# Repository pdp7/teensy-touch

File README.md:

# Teensy LC cap touch demo
Capactive touch button demo board for Teensy LC with Adafruit 128x64 OLED (SPI)

## OSH Park Shared Project:
* **[Teensy LC cap touch demo](https://oshpark.com/projects/ro7ypcxO)**
   * This is what was ordered and tested
   * File: [teensy-touch.kicad_pcb](https://github.com/pdp7/teensy-touch/blob/5fb2f44a5e37c01898689bddd4195240e6bf3efe/hardware/teensy-touch.kicad_pcb)
   * Commit: [5fb2f44 *connect GND pin for OLED to GND plane*
](https://github.com/pdp7/teensy-touch/commit/5fb2f44a5e37c01898689bddd4195240e6bf3efe)

## Bill of Materials:
* [Monochrome 0.96" 128x64 OLED graphic display](https://www.adafruit.com/product/326)
* [Teensy LC, OSH Park edition](http://store.oshpark.com/products/teensy-lc)

## Videos
* [Short demo](https://www.youtube.com/watch?v=SUqngf3_1D0)
* [Full demo](https://youtu.be/iRWQk5bGx8w)

## Photos
* [Google+ gallery](https://plus.google.com/photos/+DrewFustini/albums/6318204370050037249)
* [images directory](images)

## License
This project released under the CERN Open Hardware v1.2 License

**Note:** `teensy-touch.ino` contains code based on:

* [Capacitive sensors with the Teensy 3.0](http://njhurst.com/blog/01356576041)
* [SSD1306 display code based on example by Paul Stoffregen](https://www.pjrc.com/teensy/td_libs_SSD1306.html)

## Contact
* Drew Fustini &lt;drew@oshpark.com&gt;

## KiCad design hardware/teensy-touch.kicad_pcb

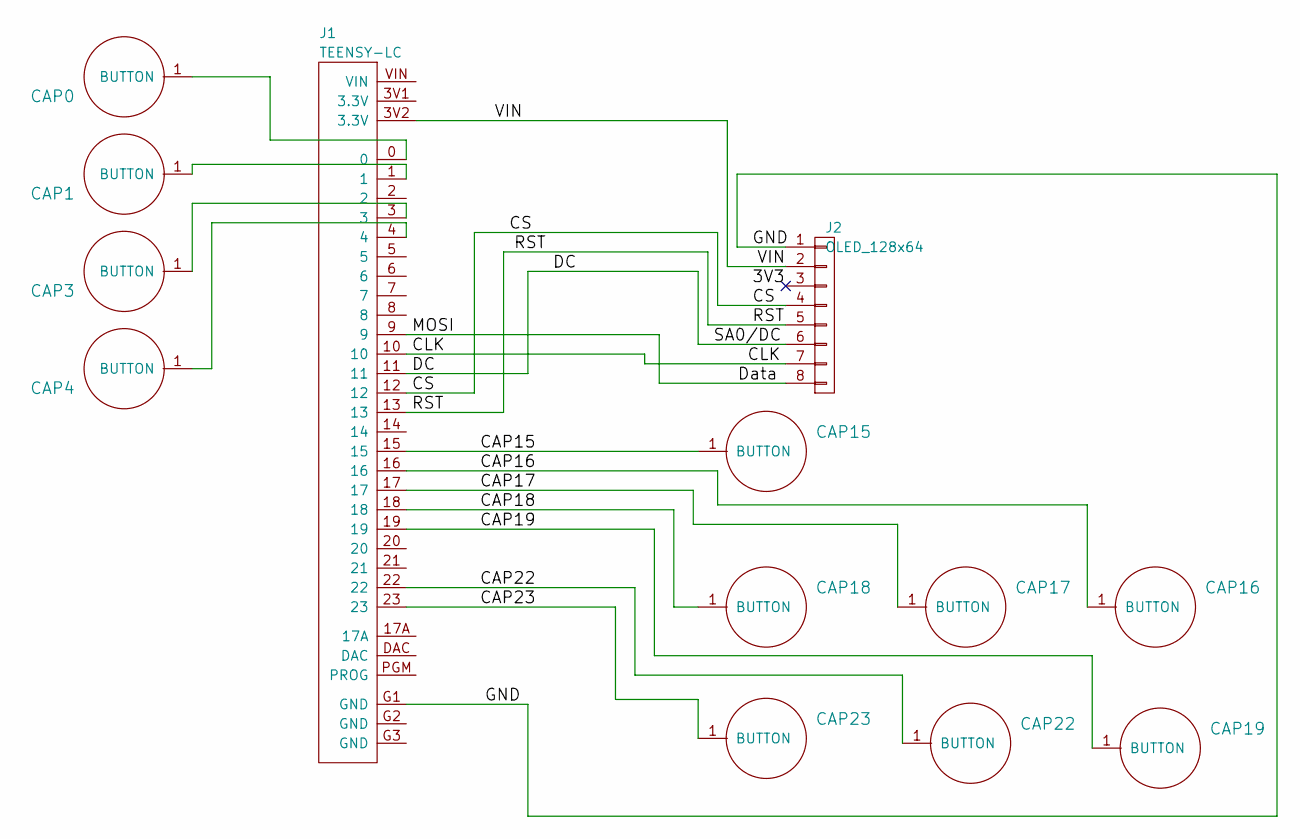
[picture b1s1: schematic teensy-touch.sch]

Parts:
CAP0, CAP1, CAP3, CAP4, CAP15, CAP16, CAP17, CAP18, CAP19, CAP22, CAP23: CAPSENSE_CIRCLE; CAPSENSE_CIRCLE_D10
J1: TEENSY-LC
J2: OLED_128x64; Pin_Header_Straight_1x08

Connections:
/CAP15: CAP15.1, J1.15
/CAP16: CAP16.1, J1.16
/CAP17: CAP17.1, J1.17
/CAP18: CAP18.1, J1.18
/CAP19: CAP19.1, J1.19
/CAP22: CAP22.1, J1.22
/CAP23: CAP23.1, J1.23
/CLK: J1.10, J2.7
/CS: J1.12, J2.4
/DC: J1.11, J2.6
/Data: J1.9, J2.8
/GND: J1.G1 (GND), J2.1
/RST: J1.13, J2.5
/VIN: J1.3V2 (3.3V), J2.2
unnamed: CAP0.1, J1.0
unnamed: CAP1.1, J1.1
unnamed: CAP3.1, J1.3
unnamed: CAP4.1, J1.4

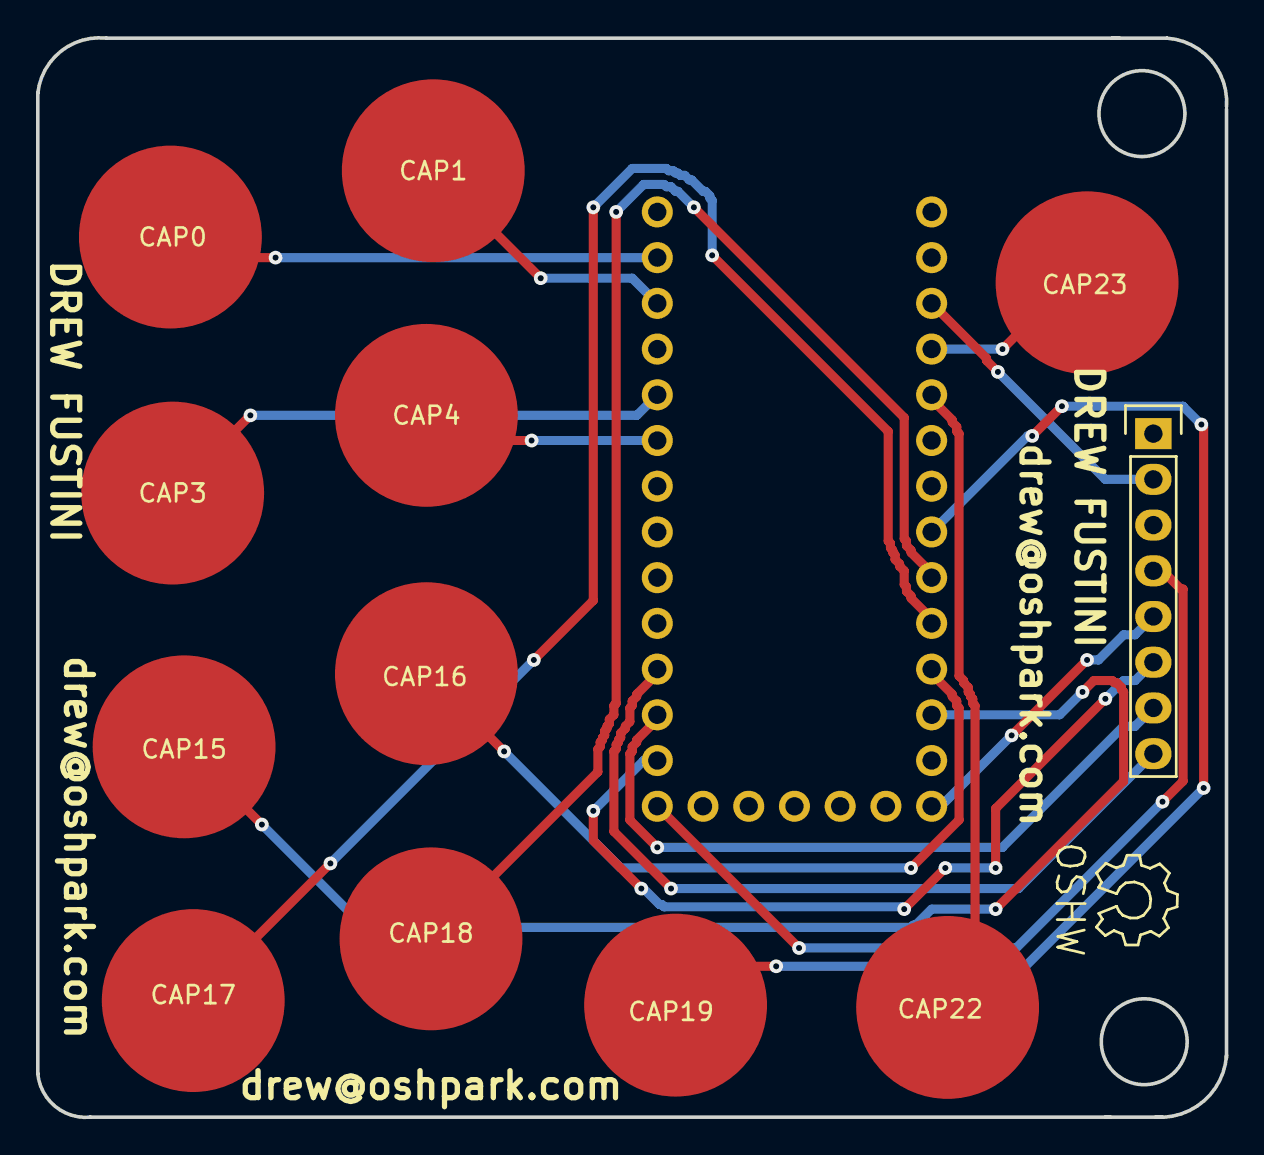
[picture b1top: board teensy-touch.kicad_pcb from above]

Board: 2 copper layers, 66.0 x 60.0 mm, 13 parts (0 on the bottom side), 18 nets.

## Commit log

2016-08-11 add LICENSE and README
2016-08-11 Add KiCad schematic and board layout
    Originally from git repo:
    https://github.com/pdp7/teensy-big-oled
2016-08-11 add OSH Park shared project link
2016-08-11 add teensy touch sketch from gist
    Original gist:
    https://gist.github.com/pdp7/6503aae568da2d0df85f56d2f1e47c5e
2016-08-11 display each cap touch button
2016-08-11 refactor display of button press
2016-08-11 improve button press handling
2016-08-18 connect GND pin for OLED to GND plane
2016-08-18 add images from Google+ gallery
    Gallery:
    https://plus.google.com/photos/+DrewFustini/albums/6318204370050037249
2016-08-18 add PCB preview from OSH Park
2016-09-16 change interval
2016-09-16 update threshold
